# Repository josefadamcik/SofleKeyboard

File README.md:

# Sofle Keyboard

Sofle is 6×4+5 keys column-staggered split keyboard with encoder support. Based on [Lily58](https://github.com/kata0510/Lily58), [Corne](https://github.com/foostan/crkbd) and [Helix](https://github.com/MakotoKurauchi/helix) keyboards.

**[For more information and documentation visit https://josefadamcik.github.io/SofleKeyboard/](https://josefadamcik.github.io/SofleKeyboard/)**

SofleKeyboard was created by [Josef Adamcik](https://josef-adamcik.cz/). The motivation and process is covered in following blog-post: [Let me introduce you SofleKeyboard - a split keyboard based on Lily58 and Crkbd](https://josef-adamcik.cz/electronics/let-me-introduce-you-sofle-keyboard-split-keyboard-based-on-lily58.html)

Sofle RGB was contributed by [Dane Evans](https://github.com/DaneEvans).

Sofle soldered was contributed by [kb-elmo](https://github.com/kb-elmo)

Sofle Pico was contributed by [Ryan Neff](https://github.com/JellyTitan)

BFS9000 was contributed by [Jesús Guillén](https://github.com/jguillen-lab)

## Firmware 

Sofle uses [QMK firmware](https://qmk.fm/)

## Default layout 

## Images of keyboard

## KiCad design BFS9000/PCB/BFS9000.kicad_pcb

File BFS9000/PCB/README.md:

# BFS9000 — Hardware

> 🇪🇸 **¿Prefieres leer esto en español?** ? [README.es.md](README.es.md)

Hardware directory for the **BFS9000** keyboard.

> **Work in progress**
>
> This hardware is currently under active development and is **not functional yet**.
> Version `0.4` should be considered an early prototype intended only for validation and iteration.
>
> Do **not** treat the current design, PCB, schematics, footprints, BOM, or documentation as final or production-ready.
> Expect breaking changes, missing features, design errors, and incomplete documentation.

## Status

- Current version: `0.4`
- Development stage: prototype / WIP
- Functional status: **not working yet**

## Notes

This directory is intended to track the ongoing hardware development of the BFS9000.
At this stage, the project is still evolving and substantial changes are expected before it becomes usable.

## License and attribution

This hardware directory is licensed under the MIT License unless otherwise stated.

BFS9000 contains original work as well as files, ideas, references, or derived work from other open-source keyboard projects and component libraries.

See:

- [LICENSE](LICENSE)
- [NOTICE.md](NOTICE.md)

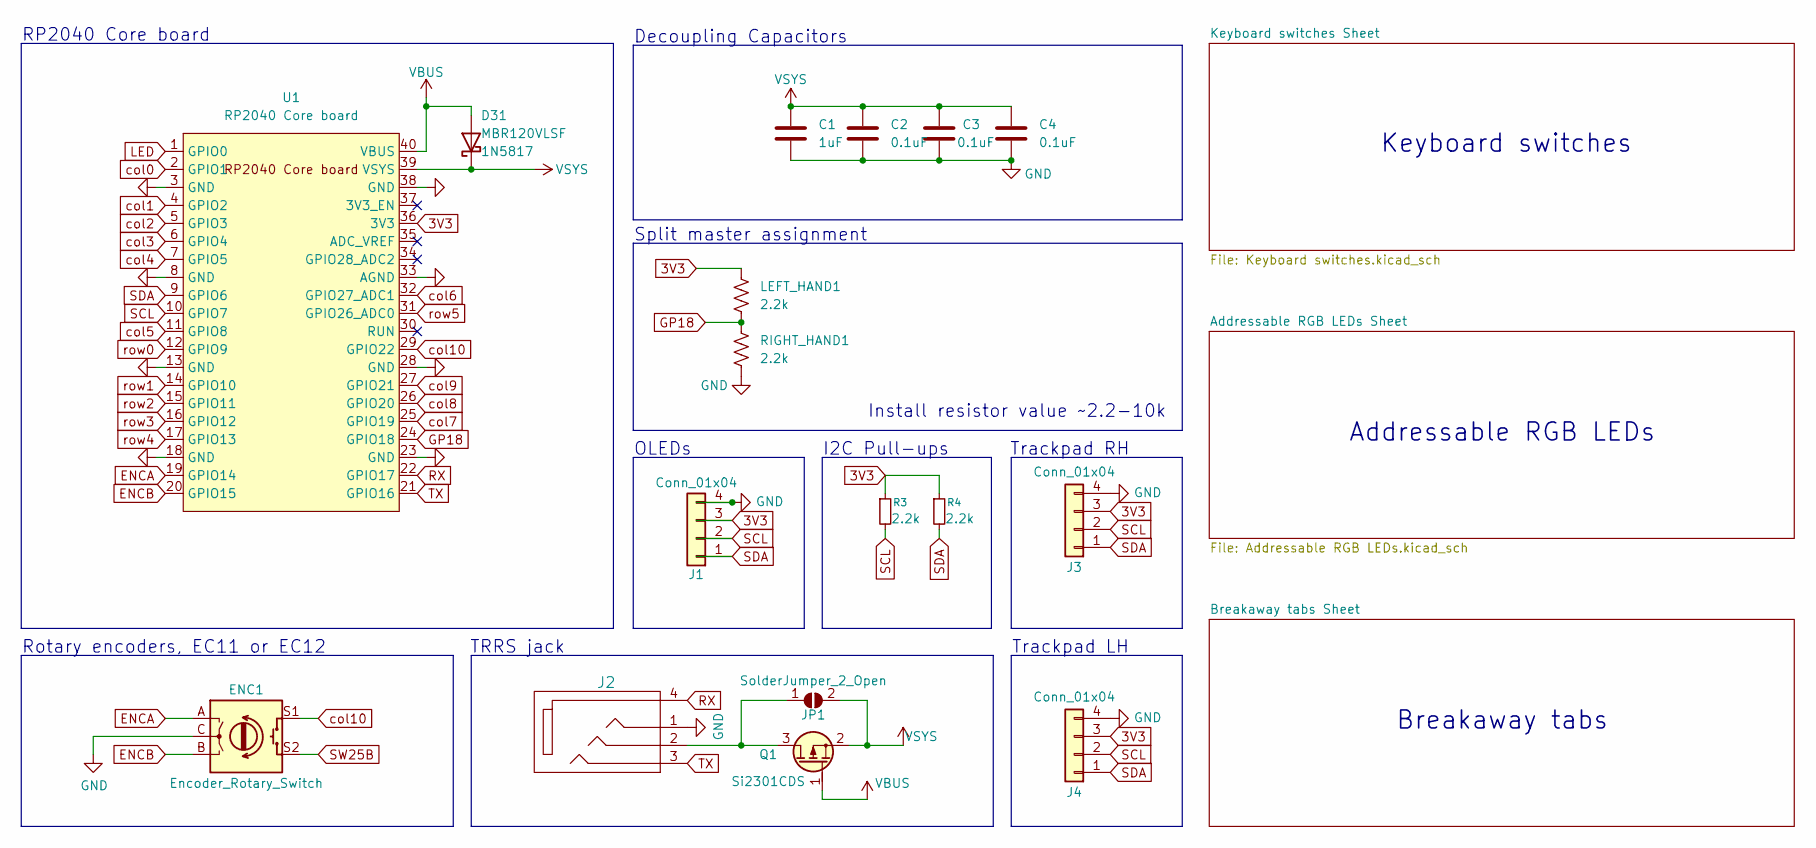
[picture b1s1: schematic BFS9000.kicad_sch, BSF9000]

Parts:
C1: 1uF; C_0805_HandSolder; Tolerance (%) 10; Voltage Rating 50V; MFG PN CL21B105KBFNNNE; JLCPCB_PN C28323
C2, C3, C4: 0.1uF; C_0805_HandSolder; Tolerance (%) 10; Voltage Rating 50V; MFG PN CC0805KRX7R9BB104; JLCPCB_PN C49678
D31: MBR120VLSF; D_Hybrid_SOD-123_DO-41_P7.62mm_DS
ENC1: Encoder_Rotary_Switch; Encoder_EC11E_Switch_Vertical_H20mm; MFG PN EC11E18244AU; JLCPCB_PN C202365
J1: Conn_01x04; Display_OLED_SSD1306_128x64; MFG PN DNP; JLCPCB_PN DNP
J2: MJ-4PP-9; MFG PN PJ-320AS; JLCPCB_PN C2939182
J3, J4: Conn_01x04; Conn_Touchpad; MFG PN DNP; JLCPCB_PN DNP
JP1: SolderJumper_2_Open; SolderJumper_Level_Shifter_Bypass; MFG PN DNP; JLCPCB_PN DNP
LEFT_HAND1: 2.2k; R_Hybrid_1206_P6.3mm; MFG PN CFR-25JB-52-2K2; JLCPCB_PN C1364486
Q1: Si2301CDS; SOT-23_DS; MFG PN SI2301CDS-T1-GE3; JLCPCB_PN C10487
R3, R4: 2.2k; R_Hybrid_1206_P6.3mm; MFG PN CFR-25JB-52-2K2; JLCPCB_PN C1364486
RIGHT_HAND1: 2.2k; R_Hybrid_1206_P6.3mm; MFG PN CFR-25JB-52-2K2; JLCPCB_PN C1364486
U1: RP2040 Core board; RPi_Pico_SMD_TH_DS; MFG PN DNP; JLCPCB_PN DNP

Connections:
3V3: J1.3, J3.3, J4.3, LEFT_HAND1.2, R3.1, R4.1, U1.36 (3V3)
ENCA: ENC1.A, U1.19 (GPIO14)
ENCB: ENC1.B, U1.20 (GPIO15)
GND: C1.2, C2.2, C3.2, C4.2, ENC1.C, J1.4, J2.1, J3.4, J4.4, RIGHT_HAND1.2, U1.3 (GND), U1.8 (GND), U1.13 (GND), U1.18 (GND), U1.23 (GND), U1.28 (GND), U1.33 (AGND), U1.38 (GND); also elsewhere on the board
GP18: LEFT_HAND1.1, RIGHT_HAND1.1, U1.24 (GPIO18)
LED: U1.1 (GPIO0); also elsewhere on the board
unnamed: J2.2, JP1.1 (A), Q1.3 (D)
RX: J2.4, U1.22 (GPIO17)
SCL: J1.2, J3.2, J4.2, R3.2, U1.10 (GPIO7)
SDA: J1.1, J3.1, J4.1, R4.2, U1.9 (GPIO6)
SW25B: ENC1.S2; also elsewhere on the board
TX: J2.3, U1.21 (GPIO16)
VBUS: D31.2 (A), Q1.1 (G), U1.40 (VBUS)
VSYS: C1.1, C2.1, C3.1, C4.1, D31.1 (K), JP1.2 (B), Q1.2 (S), U1.39 (VSYS); also elsewhere on the board
col0: U1.2 (GPIO1); also elsewhere on the board
col1: U1.4 (GPIO2); also elsewhere on the board
col2: U1.5 (GPIO3); also elsewhere on the board
col3: U1.6 (GPIO4); also elsewhere on the board
col4: U1.7 (GPIO5); also elsewhere on the board
col5: U1.11 (GPIO8); also elsewhere on the board
col6: U1.32 (GPIO27_ADC1); also elsewhere on the board
col7: U1.25 (GPIO19); also elsewhere on the board
col8: U1.26 (GPIO20); also elsewhere on the board
col9: U1.27 (GPIO21); also elsewhere on the board
col10: ENC1.S1, U1.29 (GPIO22); also elsewhere on the board
row0: U1.12 (GPIO9); also elsewhere on the board
row1: U1.14 (GPIO10); also elsewhere on the board
row2: U1.15 (GPIO11); also elsewhere on the board
row3: U1.16 (GPIO12); also elsewhere on the board
row4: U1.17 (GPIO13); also elsewhere on the board
row5: U1.31 (GPIO26_ADC0); also elsewhere on the board

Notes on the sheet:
Rotary encoders, EC11 or EC12
OLEDs
Install resistor value ~2.2-10k
Split master assignment
I2C Pull-ups
Breakaway tabs
TRRS jack
Keyboard switches
RP2040 Core board
Trackpad LH
Trackpad RH
Addressable RGB LEDs
Decoupling Capacitors

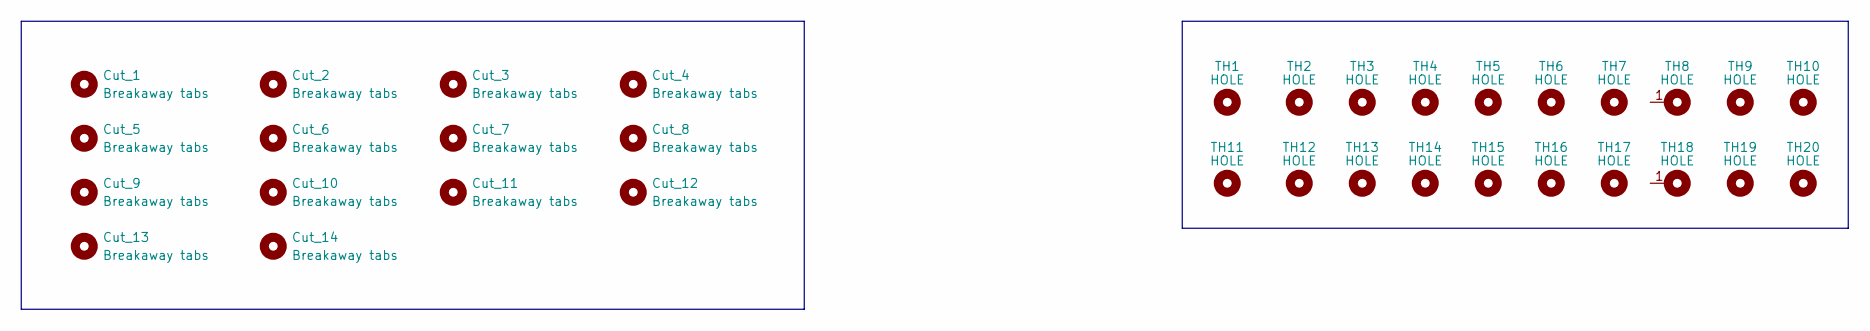
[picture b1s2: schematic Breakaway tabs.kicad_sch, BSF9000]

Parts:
Cut_1, Cut_2, Cut_3, Cut_4, Cut_5, Cut_6, Cut_7, Cut_8, Cut_9, Cut_10, Cut_11, Cut_12, Cut_13, Cut_14: Breakaway tabs; Cutout_Long_Oval; MFR.Part # DNP; JLCPCB Part # DNP
TH1, TH2, TH4, TH5: HOLE; Mount_M2_Post_Hole_Keyplate_Narrow; MFG PN DNP; JLCPCB_PN DNP
TH3, TH6, TH7, TH9, TH10, TH11, TH12, TH13, TH14, TH15, TH16, TH17, TH19, TH20: HOLE; Mount_M2_Post_Hole_Keyplate_Wide; MFG PN DNP; JLCPCB_PN DNP
TH8, TH18: HOLE; Mount_Tenting_Puck; MFG PN DNP; JLCPCB_PN DNP

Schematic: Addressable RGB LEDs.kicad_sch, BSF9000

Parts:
J5, J6: Conn_01x01; PinHeader_1x01_P2.54mm; MFG PN DNP; JLCPCB_PN DNP
MLED1, MLED2, MLED3, MLED4, MLED5, MLED6, MLED7, MLED8, MLED9, MLED10, MLED11, MLED12, MLED13, MLED14, MLED15, MLED16, MLED17, MLED18, MLED19, MLED20, MLED21, MLED22, MLED23, MLED24, MLED25, MLED26, MLED27, MLED28, MLED29: SK6803 MINI-E; Cust_SK6803_MINI-E_BFS9000; MFG PN SK6803MINI-E-001; JLCPCB_PN C5242955
MULED1, MULED2, MULED3: SK6803 MINI-E; Cust_SK6803_MINI-E_BFS9000_Underglow; MFG PN SK6803MINI-E-001; JLCPCB_PN C5242955
SLED1, SLED2, SLED3, SLED4, SLED5, SLED6, SLED7, SLED8, SLED9, SLED10, SLED11, SLED12, SLED13, SLED14, SLED15, SLED16, SLED17, SLED18, SLED19, SLED20, SLED21, SLED22: SK6803 MINI-E; Cust_SK6803_MINI-E_BFS9000; MFG PN SK6803MINI-E-001; JLCPCB_PN C5242955
SULED1, SULED2: SK6803 MINI-E; Cust_SK6803_MINI-E_BFS9000_Underglow; MFG PN SK6803MINI-E-001; JLCPCB_PN C5242955
TLED1, TLED2, TLED3, TLED4, TLED5, TLED6: SK6803 MINI-E; Cust_SK6803_MINI-E_BFS9000; MFG PN SK6803MINI-E-001; JLCPCB_PN C5242955

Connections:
GND: MLED1.1 (GND), MLED2.1 (GND), MLED3.1 (GND), MLED4.1 (GND), MLED5.1 (GND), MLED6.1 (GND), MLED7.1 (GND), MLED8.1 (GND), MLED9.1 (GND), MLED10.1 (GND), MLED11.1 (GND), MLED12.1 (GND), MLED13.1 (GND), MLED14.1 (GND), MLED15.1 (GND), MLED16.1 (GND), MLED17.1 (GND), MLED18.1 (GND), MLED19.1 (GND), MLED20.1 (GND), MLED21.1 (GND), MLED22.1 (GND), MLED23.1 (GND), MLED24.1 (GND), MLED25.1 (GND), MLED26.1 (GND), MLED27.1 (GND), MLED28.1 (GND), MLED29.1 (GND), MULED1.1 (GND), MULED2.1 (GND), MULED3.1 (GND), SLED1.1 (GND), SLED2.1 (GND), SLED3.1 (GND), SLED4.1 (GND), SLED5.1 (GND), SLED6.1 (GND), SLED7.1 (GND), SLED8.1 (GND), SLED9.1 (GND), SLED10.1 (GND), SLED11.1 (GND), SLED12.1 (GND), SLED13.1 (GND), SLED14.1 (GND), SLED15.1 (GND), SLED16.1 (GND), SLED17.1 (GND), SLED18.1 (GND), SLED19.1 (GND), SLED20.1 (GND), SLED21.1 (GND), SLED22.1 (GND), SULED1.1 (GND), SULED2.1 (GND), TLED1.1 (GND), TLED2.1 (GND), TLED3.1 (GND), TLED4.1 (GND), TLED5.1 (GND), TLED6.1 (GND); also elsewhere on the board
LED: MLED1.2 (DIN); also elsewhere on the board
LED_N: J6.1 (Pin_1_1), SLED1.2 (DIN), TLED6.4 (DOUT)
LED_T: J5.1 (Pin_1_1), MULED3.4 (DOUT), TLED1.2 (DIN)
LED_U: MLED29.4 (DOUT), MULED1.2 (DIN)
unnamed: MLED1.4 (DOUT), MLED2.2 (DIN)
unnamed: MLED2.4 (DOUT), MLED3.2 (DIN)
unnamed: MLED3.4 (DOUT), MLED4.2 (DIN)
unnamed: MLED4.4 (DOUT), MLED5.2 (DIN)
unnamed: MLED5.4 (DOUT), MLED6.2 (DIN)
unnamed: MLED6.4 (DOUT), MLED7.2 (DIN)
unnamed: MLED7.4 (DOUT), MLED8.2 (DIN)
unnamed: MLED8.4 (DOUT), MLED9.2 (DIN)
unnamed: MLED9.4 (DOUT), MLED10.2 (DIN)
unnamed: MLED10.4 (DOUT), MLED11.2 (DIN)
unnamed: MLED11.4 (DOUT), MLED12.2 (DIN)
unnamed: MLED12.4 (DOUT), MLED13.2 (DIN)
unnamed: MLED13.4 (DOUT), MLED14.2 (DIN)
unnamed: MLED14.4 (DOUT), MLED15.2 (DIN)
unnamed: MLED15.4 (DOUT), MLED16.2 (DIN)
unnamed: MLED16.4 (DOUT), MLED17.2 (DIN)
unnamed: MLED17.4 (DOUT), MLED18.2 (DIN)
unnamed: MLED18.4 (DOUT), MLED19.2 (DIN)
unnamed: MLED19.4 (DOUT), MLED20.2 (DIN)
unnamed: MLED20.4 (DOUT), MLED21.2 (DIN)
unnamed: MLED21.4 (DOUT), MLED22.2 (DIN)
unnamed: MLED22.4 (DOUT), MLED23.2 (DIN)
unnamed: MLED23.4 (DOUT), MLED24.2 (DIN)
unnamed: MLED24.4 (DOUT), MLED25.2 (DIN)
unnamed: MLED25.4 (DOUT), MLED26.2 (DIN)
unnamed: MLED26.4 (DOUT), MLED27.2 (DIN)
unnamed: MLED27.4 (DOUT), MLED28.2 (DIN)
unnamed: MLED28.4 (DOUT), MLED29.2 (DIN)
unnamed: MULED1.4 (DOUT), MULED2.2 (DIN)
unnamed: MULED2.4 (DOUT), MULED3.2 (DIN)
unnamed: SLED1.4 (DOUT), SLED2.2 (DIN)
unnamed: SLED2.4 (DOUT), SLED3.2 (DIN)
unnamed: SLED3.4 (DOUT), SLED4.2 (DIN)
unnamed: SLED4.4 (DOUT), SLED5.2 (DIN)
unnamed: SLED5.4 (DOUT), SLED6.2 (DIN)
unnamed: SLED6.4 (DOUT), SLED7.2 (DIN)
unnamed: SLED7.4 (DOUT), SLED8.2 (DIN)
unnamed: SLED8.4 (DOUT), SLED9.2 (DIN)
unnamed: SLED9.4 (DOUT), SLED10.2 (DIN)
unnamed: SLED10.4 (DOUT), SLED11.2 (DIN)
unnamed: SLED11.4 (DOUT), SLED12.2 (DIN)
unnamed: SLED12.4 (DOUT), SLED13.2 (DIN)
unnamed: SLED13.4 (DOUT), SLED14.2 (DIN)
unnamed: SLED14.4 (DOUT), SLED15.2 (DIN)
unnamed: SLED15.4 (DOUT), SLED16.2 (DIN)
unnamed: SLED16.4 (DOUT), SLED17.2 (DIN)
unnamed: SLED17.4 (DOUT), SLED18.2 (DIN)
unnamed: SLED18.4 (DOUT), SLED19.2 (DIN)
unnamed: SLED19.4 (DOUT), SLED20.2 (DIN)
unnamed: SLED20.4 (DOUT), SLED21.2 (DIN)
unnamed: SLED21.4 (DOUT), SLED22.2 (DIN)
unnamed: SULED1.4 (DOUT), SULED2.2 (DIN)
unnamed: TLED1.4 (DOUT), TLED2.2 (DIN)
unnamed: TLED2.4 (DOUT), TLED3.2 (DIN)
unnamed: TLED3.4 (DOUT), TLED4.2 (DIN)
unnamed: TLED4.4 (DOUT), TLED5.2 (DIN)
unnamed: TLED5.4 (DOUT), TLED6.2 (DIN)
VSYS: MLED1.3 (VDD), MLED2.3 (VDD), MLED3.3 (VDD), MLED4.3 (VDD), MLED5.3 (VDD), MLED6.3 (VDD), MLED7.3 (VDD), MLED8.3 (VDD), MLED9.3 (VDD), MLED10.3 (VDD), MLED11.3 (VDD), MLED12.3 (VDD), MLED13.3 (VDD), MLED14.3 (VDD), MLED15.3 (VDD), MLED16.3 (VDD), MLED17.3 (VDD), MLED18.3 (VDD), MLED19.3 (VDD), MLED20.3 (VDD), MLED21.3 (VDD), MLED22.3 (VDD), MLED23.3 (VDD), MLED24.3 (VDD), MLED25.3 (VDD), MLED26.3 (VDD), MLED27.3 (VDD), MLED28.3 (VDD), MLED29.3 (VDD), MULED1.3 (VDD), MULED2.3 (VDD), MULED3.3 (VDD), SLED1.3 (VDD), SLED2.3 (VDD), SLED3.3 (VDD), SLED4.3 (VDD), SLED5.3 (VDD), SLED6.3 (VDD), SLED7.3 (VDD), SLED8.3 (VDD), SLED9.3 (VDD), SLED10.3 (VDD), SLED11.3 (VDD), SLED12.3 (VDD), SLED13.3 (VDD), SLED14.3 (VDD), SLED15.3 (VDD), SLED16.3 (VDD), SLED17.3 (VDD), SLED18.3 (VDD), SLED19.3 (VDD), SLED20.3 (VDD), SLED21.3 (VDD), SLED22.3 (VDD), SULED1.3 (VDD), SULED2.3 (VDD), TLED1.3 (VDD), TLED2.3 (VDD), TLED3.3 (VDD), TLED4.3 (VDD), TLED5.3 (VDD), TLED6.3 (VDD); also elsewhere on the board
nLED_U: SLED22.4 (DOUT), SULED1.2 (DIN)

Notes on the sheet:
All LEDs

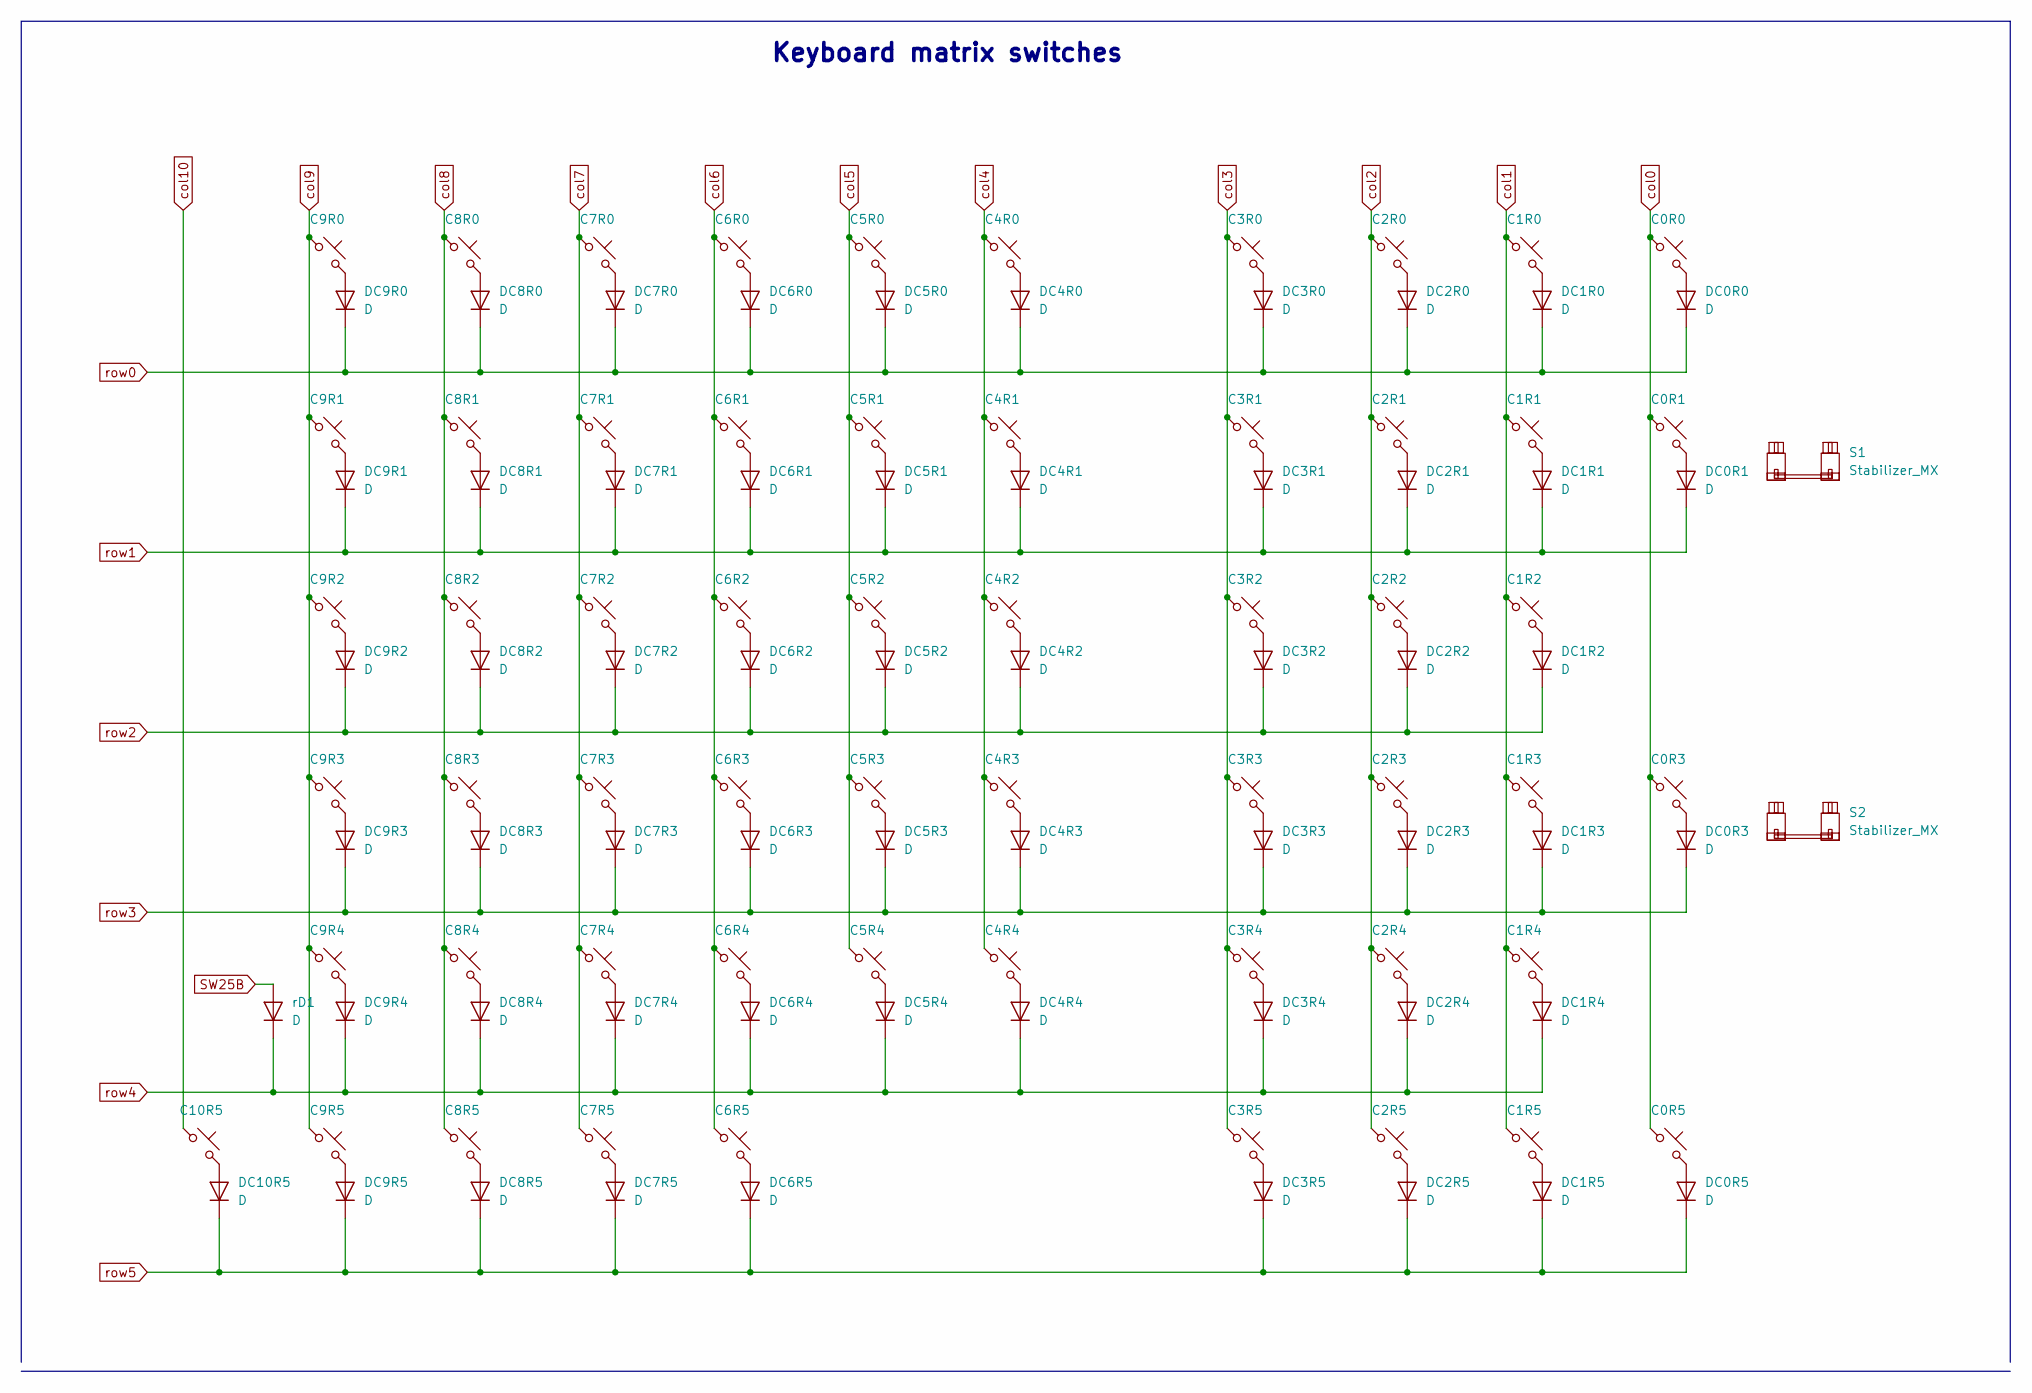
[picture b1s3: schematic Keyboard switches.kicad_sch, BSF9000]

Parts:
C0R0, C0R1, C0R3, C0R5, C1R0, C1R1, C1R2, C1R3, C1R4, C1R5, C2R0, C2R1, C2R2, C2R3, C2R4, C2R5, C3R0, C3R1, C3R2, C3R3, C3R4, C3R5, C4R0, C4R1, C4R2, C4R3, C4R4, C5R0, C5R1, C5R2, C5R3, C5R4, C6R0, C6R1, C6R2, C6R3, C6R4, C6R5, C7R0, C7R1, C7R2, C7R3, C7R4, C7R5, C8R0, C8R1, C8R2, C8R3, C8R4, C8R5, C9R0, C9R1, C9R2, C9R3, C9R4, C9R5, C10R5: MX_SW_HS; SW_Cherry_MX_Hotswap_DS; MFG PN CPG151101S11-16; JLCPCB_PN C41430893
DC0R0, DC0R1, DC0R3, DC0R5, DC1R0, DC1R1, DC1R2, DC1R3, DC1R4, DC1R5, DC2R0, DC2R1, DC2R2, DC2R3, DC2R4, DC2R5, DC3R0, DC3R1, DC3R2, DC3R3, DC3R4, DC3R5, DC4R0, DC4R1, DC4R2, DC4R3, DC4R4, DC5R0, DC5R1, DC5R2, DC5R3, DC5R4, DC6R0, DC6R1, DC6R2, DC6R3, DC6R4, DC6R5, DC7R0, DC7R1, DC7R2, DC7R3, DC7R4, DC7R5, DC8R0, DC8R1, DC8R2, DC8R3, DC8R4, DC8R5, DC9R0, DC9R1, DC9R2, DC9R3, DC9R4, DC9R5, DC10R5: D; D_Hybrid_SOD-123_DO-35_DS; Voltage Rating 75v; MFG PN 1N4148W; JLCPCB_PN C81598
S1, S2: Stabilizer_MX; Stabilizer_MX_2u; MFG PN DNP; JLCPCB_PN DNP
rD1: D; D_Hybrid_SOD-123_DO-35_DS; Voltage Rating 75v; MFG PN 1N4148W; JLCPCB_PN C81598

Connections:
unnamed: C0R0.2, DC0R0.2 (A)
unnamed: C0R1.2, DC0R1.2 (A)
unnamed: C0R3.2, DC0R3.2 (A)
unnamed: C0R5.2, DC0R5.2 (A)
unnamed: C1R0.2, DC1R0.2 (A)
unnamed: C1R1.2, DC1R1.2 (A)
unnamed: C1R2.2, DC1R2.2 (A)
unnamed: C1R3.2, DC1R3.2 (A)
unnamed: C1R4.2, DC1R4.2 (A)
unnamed: C1R5.2, DC1R5.2 (A)
unnamed: C2R0.2, DC2R0.2 (A)
unnamed: C2R1.2, DC2R1.2 (A)
unnamed: C2R2.2, DC2R2.2 (A)
unnamed: C2R3.2, DC2R3.2 (A)
unnamed: C2R4.2, DC2R4.2 (A)
unnamed: C2R5.2, DC2R5.2 (A)
unnamed: C3R0.2, DC3R0.2 (A)
unnamed: C3R1.2, DC3R1.2 (A)
unnamed: C3R2.2, DC3R2.2 (A)
unnamed: C3R3.2, DC3R3.2 (A)
unnamed: C3R4.2, DC3R4.2 (A)
unnamed: C3R5.2, DC3R5.2 (A)
unnamed: C4R0.2, DC4R0.2 (A)
unnamed: C4R1.2, DC4R1.2 (A)
unnamed: C4R2.2, DC4R2.2 (A)
unnamed: C4R3.2, DC4R3.2 (A)
unnamed: C4R4.2, DC4R4.2 (A)
unnamed: C5R0.2, DC5R0.2 (A)
unnamed: C5R1.2, DC5R1.2 (A)
unnamed: C5R2.2, DC5R2.2 (A)
unnamed: C5R3.2, DC5R3.2 (A)
unnamed: C5R4.2, DC5R4.2 (A)
unnamed: C6R0.2, DC6R0.2 (A)
unnamed: C6R1.2, DC6R1.2 (A)
unnamed: C6R2.2, DC6R2.2 (A)
unnamed: C6R3.2, DC6R3.2 (A)
unnamed: C6R4.2, DC6R4.2 (A)
unnamed: C6R5.2, DC6R5.2 (A)
unnamed: C7R0.2, DC7R0.2 (A)
unnamed: C7R1.2, DC7R1.2 (A)
unnamed: C7R2.2, DC7R2.2 (A)
unnamed: C7R3.2, DC7R3.2 (A)
unnamed: C7R4.2, DC7R4.2 (A)
unnamed: C7R5.2, DC7R5.2 (A)
unnamed: C8R0.2, DC8R0.2 (A)
unnamed: C8R1.2, DC8R1.2 (A)
unnamed: C8R2.2, DC8R2.2 (A)
unnamed: C8R3.2, DC8R3.2 (A)
unnamed: C8R4.2, DC8R4.2 (A)
unnamed: C8R5.2, DC8R5.2 (A)
unnamed: C9R0.2, DC9R0.2 (A)
unnamed: C9R1.2, DC9R1.2 (A)
unnamed: C9R2.2, DC9R2.2 (A)
unnamed: C9R3.2, DC9R3.2 (A)
unnamed: C9R4.2, DC9R4.2 (A)
unnamed: C9R5.2, DC9R5.2 (A)
unnamed: C10R5.2, DC10R5.2 (A)
SW25B: rD1.2 (A); also elsewhere on the board
col0: C0R0.1, C0R1.1, C0R3.1, C0R5.1; also elsewhere on the board
col1: C1R0.1, C1R1.1, C1R2.1, C1R3.1, C1R4.1, C1R5.1; also elsewhere on the board
col2: C2R0.1, C2R1.1, C2R2.1, C2R3.1, C2R4.1, C2R5.1; also elsewhere on the board
col3: C3R0.1, C3R1.1, C3R2.1, C3R3.1, C3R4.1, C3R5.1; also elsewhere on the board
col4: C4R0.1, C4R1.1, C4R2.1, C4R3.1, C4R4.1; also elsewhere on the board
col5: C5R0.1, C5R1.1, C5R2.1, C5R3.1, C5R4.1; also elsewhere on the board
col6: C6R0.1, C6R1.1, C6R2.1, C6R3.1, C6R4.1, C6R5.1; also elsewhere on the board
col7: C7R0.1, C7R1.1, C7R2.1, C7R3.1, C7R4.1, C7R5.1; also elsewhere on the board
col8: C8R0.1, C8R1.1, C8R2.1, C8R3.1, C8R4.1, C8R5.1; also elsewhere on the board
col9: C9R0.1, C9R1.1, C9R2.1, C9R3.1, C9R4.1, C9R5.1; also elsewhere on the board
col10: C10R5.1; also elsewhere on the board
row0: DC0R0.1 (K), DC1R0.1 (K), DC2R0.1 (K), DC3R0.1 (K), DC4R0.1 (K), DC5R0.1 (K), DC6R0.1 (K), DC7R0.1 (K), DC8R0.1 (K), DC9R0.1 (K); also elsewhere on the board
row1: DC0R1.1 (K), DC1R1.1 (K), DC2R1.1 (K), DC3R1.1 (K), DC4R1.1 (K), DC5R1.1 (K), DC6R1.1 (K), DC7R1.1 (K), DC8R1.1 (K), DC9R1.1 (K); also elsewhere on the board
row2: DC1R2.1 (K), DC2R2.1 (K), DC3R2.1 (K), DC4R2.1 (K), DC5R2.1 (K), DC6R2.1 (K), DC7R2.1 (K), DC8R2.1 (K), DC9R2.1 (K); also elsewhere on the board
row3: DC0R3.1 (K), DC1R3.1 (K), DC2R3.1 (K), DC3R3.1 (K), DC4R3.1 (K), DC5R3.1 (K), DC6R3.1 (K), DC7R3.1 (K), DC8R3.1 (K), DC9R3.1 (K); also elsewhere on the board
row4: DC1R4.1 (K), DC2R4.1 (K), DC3R4.1 (K), DC4R4.1 (K), DC5R4.1 (K), DC6R4.1 (K), DC7R4.1 (K), DC8R4.1 (K), DC9R4.1 (K), rD1.1 (K); also elsewhere on the board
row5: DC0R5.1 (K), DC1R5.1 (K), DC2R5.1 (K), DC3R5.1 (K), DC6R5.1 (K), DC7R5.1 (K), DC8R5.1 (K), DC9R5.1 (K), DC10R5.1 (K); also elsewhere on the board

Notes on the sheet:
Keyboard matrix switches

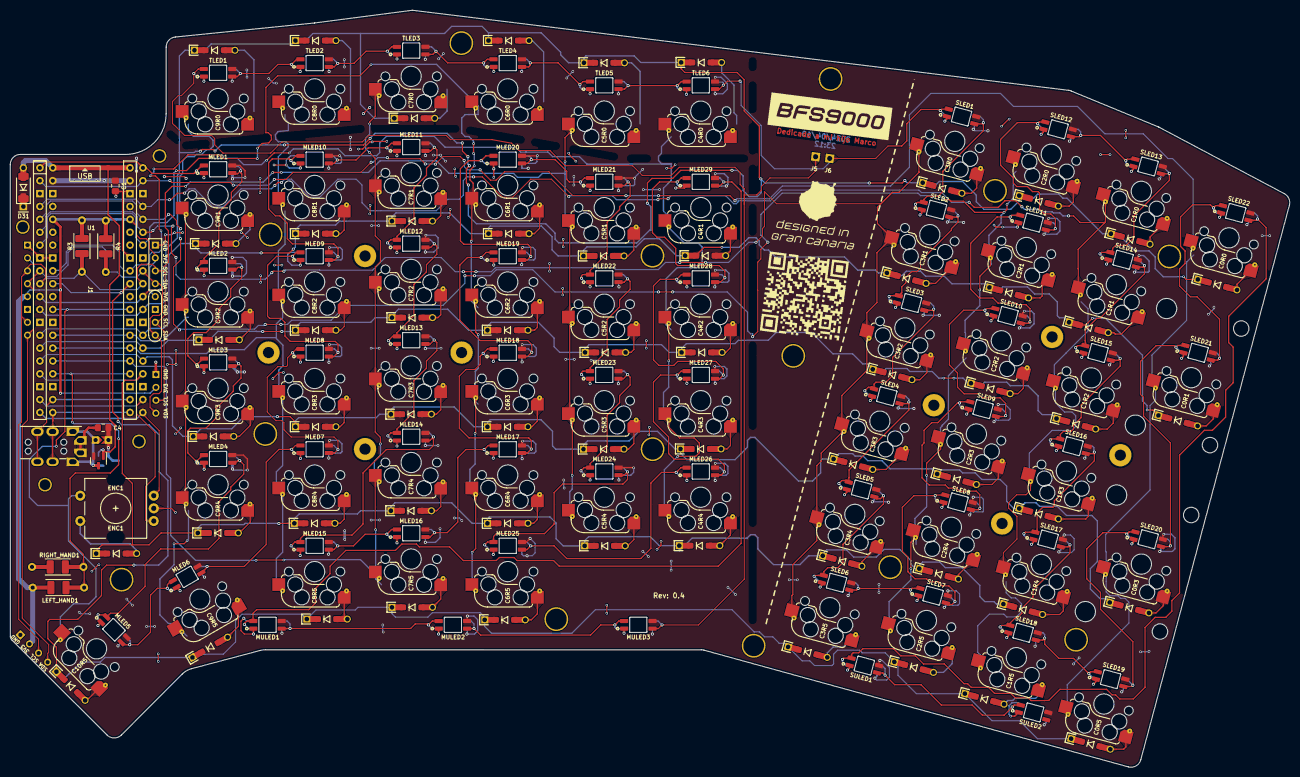
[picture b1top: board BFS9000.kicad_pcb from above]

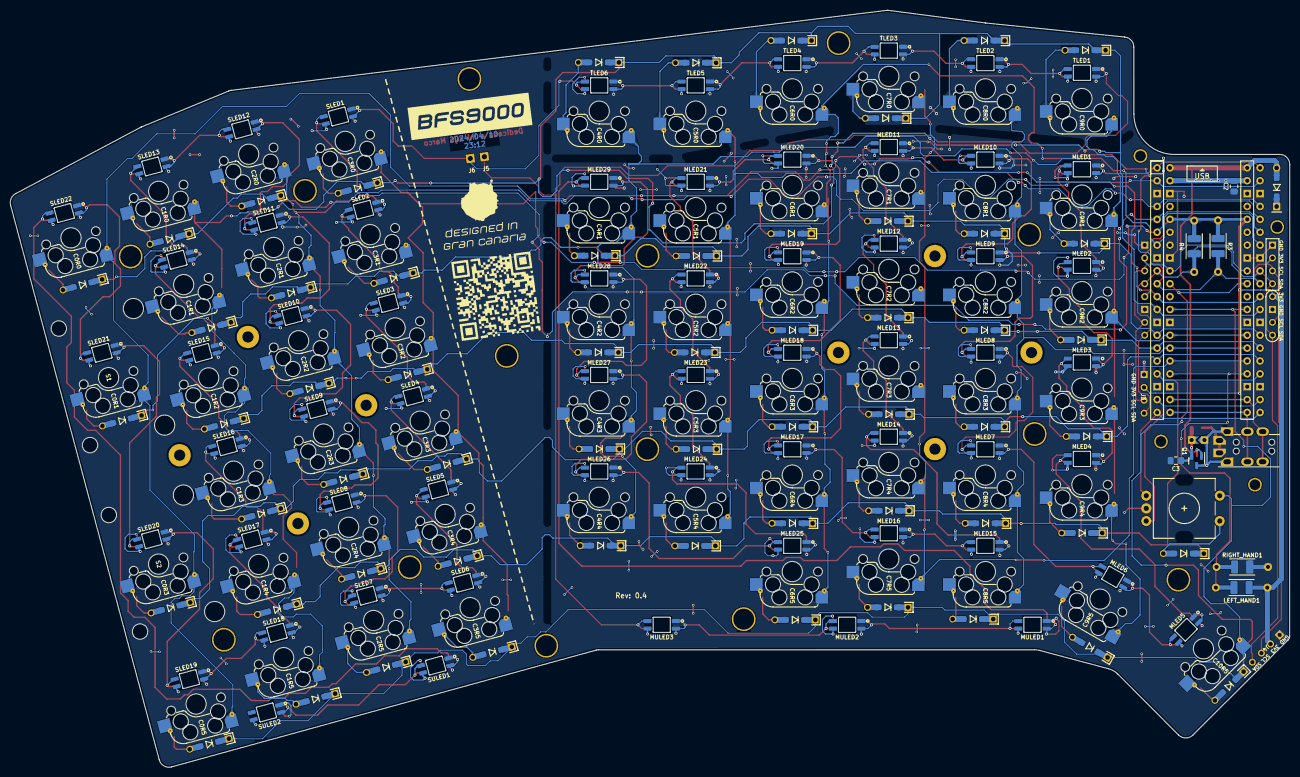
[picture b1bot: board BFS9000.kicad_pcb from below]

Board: 2 copper layers, 252.5 x 149.4 mm, 237 parts (188 on the bottom side), 149 nets.

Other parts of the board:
BFS9000_Back, BFS9000_Front: LOGO; Logo_BFS9000_Gran_Canaria
D31_B: D_SOD-128
Wiki_Back: QR; QR_Wiki
Wiki_Front: QR; QR_Wiki

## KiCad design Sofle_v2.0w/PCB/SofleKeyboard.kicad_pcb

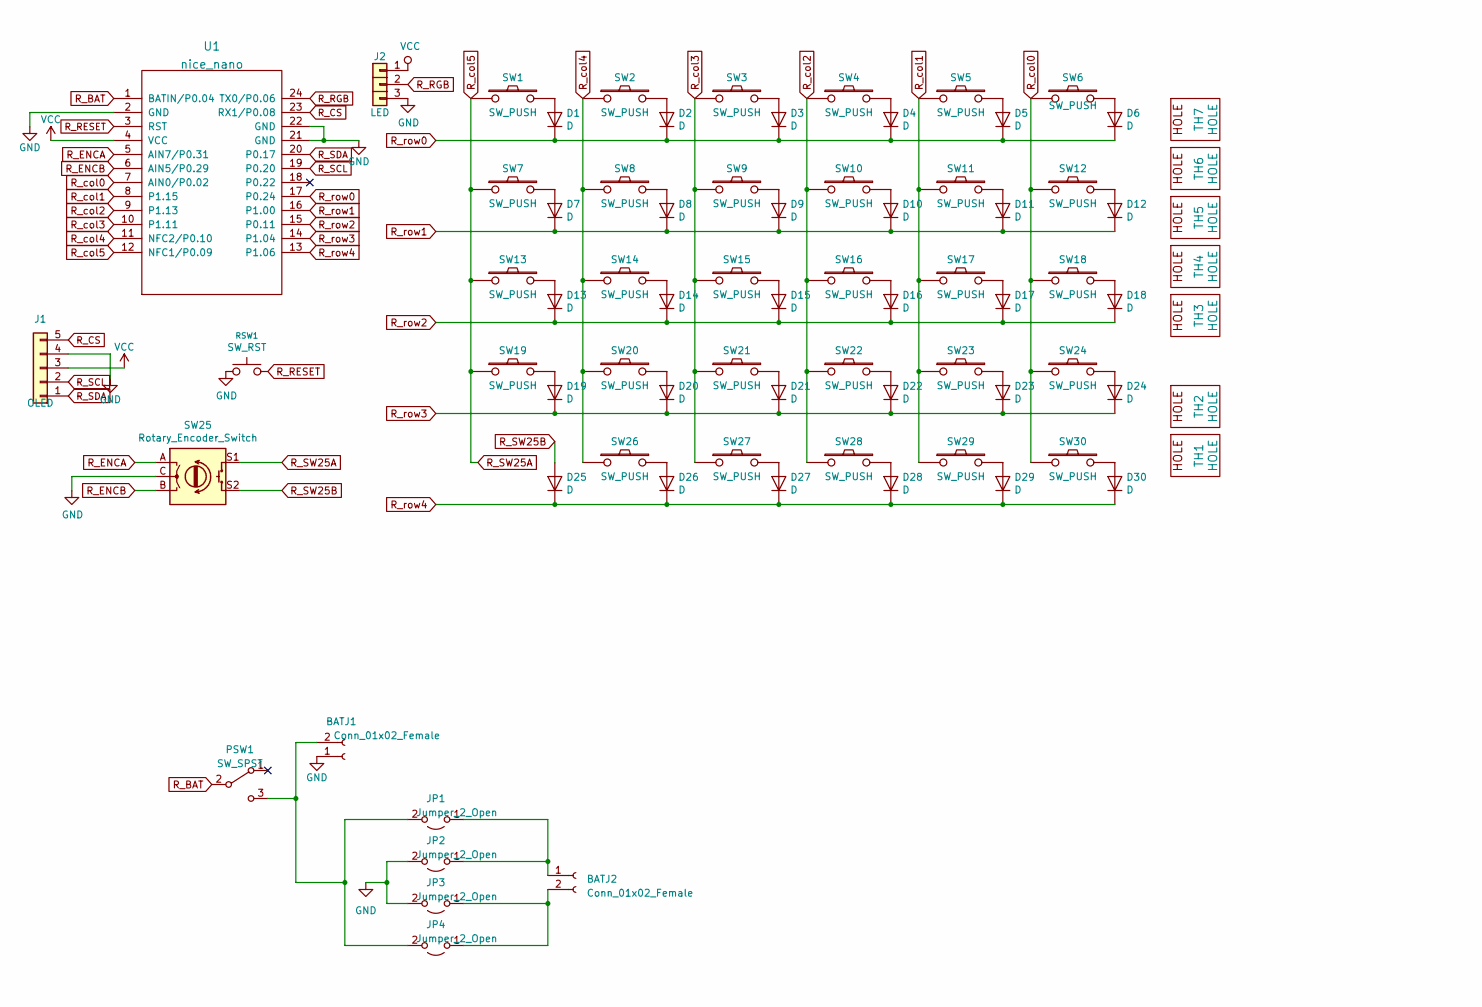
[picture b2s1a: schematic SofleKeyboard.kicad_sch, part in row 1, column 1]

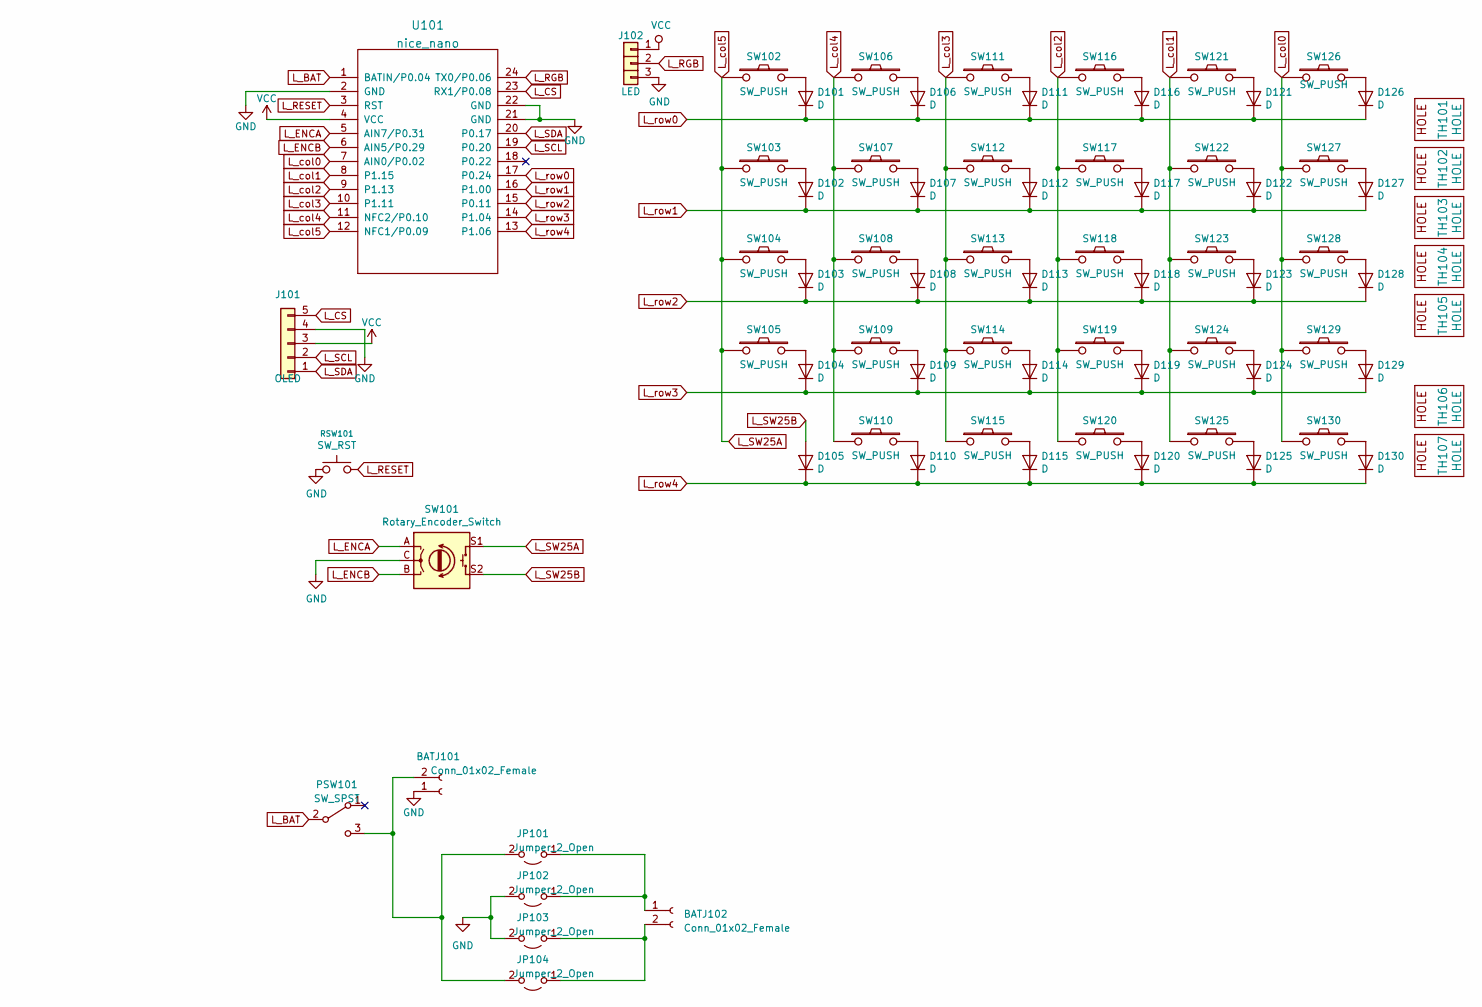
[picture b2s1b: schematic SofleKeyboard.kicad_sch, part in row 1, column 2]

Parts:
BATJ1, BATJ101: Conn_01x02_Female; PinHeader_1x02_P2.54mm_Vertical
BATJ2, BATJ102: Conn_01x02_Female; JST_PH_S2B-PH-K_1x02_P2.00mm_Horizontal
D1, D2, D3, D4, D5, D6, D7, D8, D9, D10, D11, D12, D13, D14, D15, D16, D17, D18, D19, D20, D21, D22, D23, D24, D25, D26, D27, D28, D29, D30, D101, D102, D103, D104, D105, D106, D107, D108, D109, D110, D111, D112, D113, D114, D115, D116, D117, D118, D119, D120, D121, D122, D123, D124, D125, D126, D127, D128, D129, D130: D; Diode_SOD123
J1, J101: OLED; nice_view
J2, J102: LED
JP1, JP2, JP3, JP4, JP101, JP102, JP103, JP104: Jumper_2_Open; SolderJumper-2_P1.3mm_Open_Pad1.0x1.5mm
PSW1, PSW101: SW_SPST; SW_SPDT_PCM12
RSW1, RSW101: SW_RST; TACT_SWITCH_TVBP06
SW1, SW2, SW3, SW4, SW5, SW6, SW7, SW8, SW9, SW10, SW11, SW12, SW13, SW14, SW15, SW16, SW17, SW18, SW19, SW20, SW21, SW22, SW23, SW24, SW27, SW28, SW29, SW30, SW102, SW103, SW104, SW105, SW106, SW107, SW108, SW109, SW111, SW112, SW113, SW114, SW115, SW116, SW117, SW118, SW119, SW120, SW121, SW122, SW123, SW124, SW125, SW126, SW127, SW128, SW129, SW130: SW_PUSH; CherryMX_KailhLowProfile_Hotswap_OneSide
SW25, SW101: Rotary_Encoder_Switch; RotaryEncoder_Alps_EC11E-Switch_Vertical_H20mm-keebio_modif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
SW26, SW110: SW_PUSH; CherryMX_KailhLowProfile_Hotswap_OneSide_1.5
TH1, TH2, TH106, TH107: HOLE; M2_HOLE_PCB
TH3, TH4, TH5, TH6, TH7, TH101, TH102, TH103, TH104, TH105: HOLE; HOLE_M2_TH
U1, U101: nice_nano; nice!nano

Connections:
GND: BATJ1.1, BATJ2.1, BATJ101.1, J1.4, J2.3, J2.4, J101.4, J102.3, JP1.1 (A), JP2.1 (A), JP2.2 (B), JP3.2 (B), JP101.1 (A), JP102.1 (A), JP102.2 (B), JP103.2 (B), RSW1.1, RSW101.1, SW25.C, SW101.C, U1.2 (GND), U1.21 (GND), U1.22 (GND), U101.2 (GND), U101.21 (GND), U101.22 (GND)
L_BAT: PSW101.2 (B), U101.1 (BATIN/P0.04)
L_CS: J101.5, U101.23 (RX1/P0.08)
L_ENCA: SW101.A, U101.5 (AIN7/P0.31)
L_ENCB: SW101.B, U101.6 (AIN5/P0.29)
L_RESET: RSW101.2, U101.3 (RST)
L_RGB: J102.2, U101.24 (TX0/P0.06)
L_SCL: J101.2, U101.19 (P0.20)
L_SDA: J101.1, U101.20 (P0.17)
L_SW25A: SW101.S1, SW102.1, SW103.1, SW104.1, SW105.1, U101.12 (NFC1/P0.09)
L_SW25B: D105.2 (A), SW101.S2
L_col0: SW126.1, SW127.1, SW128.1, SW129.1, SW130.1, U101.7 (AIN0/P0.02)
L_col1: SW121.1, SW122.1, SW123.1, SW124.1, SW125.1, U101.8 (P1.15)
L_col2: SW116.1, SW117.1, SW118.1, SW119.1, SW120.1, U101.9 (P1.13)
L_col3: SW111.1, SW112.1, SW113.1, SW114.1, SW115.1, U101.10 (P1.11)
L_col4: SW106.1, SW107.1, SW108.1, SW109.1, SW110.1, U101.11 (NFC2/P0.10)
L_row0: D101.1 (K), D106.1 (K), D111.1 (K), D116.1 (K), D121.1 (K), D126.1 (K), U101.17 (P0.24)
L_row1: D102.1 (K), D107.1 (K), D112.1 (K), D117.1 (K), D122.1 (K), D127.1 (K), U101.16 (P1.00)
L_row2: D103.1 (K), D108.1 (K), D113.1 (K), D118.1 (K), D123.1 (K), D128.1 (K), U101.15 (P0.11)
L_row3: D104.1 (K), D109.1 (K), D114.1 (K), D119.1 (K), D124.1 (K), D129.1 (K), U101.14 (P1.04)
L_row4: D105.1 (K), D110.1 (K), D115.1 (K), D120.1 (K), D125.1 (K), D130.1 (K), U101.13 (P1.06)
unnamed: BATJ1.2, BATJ2.2, JP1.2 (B), JP3.1 (A), JP4.1 (A), JP4.2 (B), JP103.1 (A), JP104.1 (A), PSW1.3 (C)
unnamed: BATJ101.2, PSW101.3 (C)
unnamed: D1.2 (A), SW1.2
unnamed: D2.2 (A), SW2.2
unnamed: D3.2 (A), SW3.2
unnamed: D4.2 (A), SW4.2
unnamed: D5.2 (A), SW5.2
unnamed: D6.2 (A), SW6.2
unnamed: D7.2 (A), SW7.2
unnamed: D8.2 (A), SW8.2
unnamed: D9.2 (A), SW9.2
unnamed: D10.2 (A), SW10.2
unnamed: D11.2 (A), SW11.2
unnamed: D12.2 (A), SW12.2
unnamed: D13.2 (A), SW13.2
unnamed: D14.2 (A), SW14.2
unnamed: D15.2 (A), SW15.2
unnamed: D16.2 (A), SW16.2
unnamed: D17.2 (A), SW17.2
unnamed: D18.2 (A), SW18.2
unnamed: D19.2 (A), SW19.2
unnamed: D20.2 (A), SW20.2
unnamed: D21.2 (A), SW21.2
unnamed: D22.2 (A), SW22.2
unnamed: D23.2 (A), SW23.2
unnamed: D24.2 (A), SW24.2
unnamed: D26.2 (A), SW26.2
unnamed: D27.2 (A), SW27.2
unnamed: D28.2 (A), SW28.2
unnamed: D29.2 (A), SW29.2
unnamed: D30.2 (A), SW30.2
unnamed: D101.2 (A), SW102.2
unnamed: D102.2 (A), SW103.2
unnamed: D103.2 (A), SW104.2
unnamed: D104.2 (A), SW105.2
unnamed: D106.2 (A), SW106.2
unnamed: D107.2 (A), SW107.2
unnamed: D108.2 (A), SW108.2
unnamed: D109.2 (A), SW109.2
unnamed: D110.2 (A), SW110.2
unnamed: D111.2 (A), SW111.2
unnamed: D112.2 (A), SW112.2
unnamed: D113.2 (A), SW113.2
unnamed: D114.2 (A), SW114.2
unnamed: D115.2 (A), SW115.2
unnamed: D116.2 (A), SW116.2
unnamed: D117.2 (A), SW117.2
unnamed: D118.2 (A), SW118.2
unnamed: D119.2 (A), SW119.2
unnamed: D120.2 (A), SW120.2
unnamed: D121.2 (A), SW121.2
unnamed: D122.2 (A), SW122.2
unnamed: D123.2 (A), SW123.2
unnamed: D124.2 (A), SW124.2
unnamed: D125.2 (A), SW125.2
unnamed: D126.2 (A), SW126.2
unnamed: D127.2 (A), SW127.2
unnamed: D128.2 (A), SW128.2
unnamed: D129.2 (A), SW129.2
unnamed: D130.2 (A), SW130.2
R_BAT: PSW1.2 (B), U1.1 (BATIN/P0.04)
R_CS: J1.5, U1.23 (RX1/P0.08)
R_ENCA: SW25.A, U1.5 (AIN7/P0.31)
R_ENCB: SW25.B, U1.6 (AIN5/P0.29)
R_RESET: RSW1.2, U1.3 (RST)
R_RGB: J2.2, U1.24 (TX0/P0.06)
R_SCL: J1.2, U1.19 (P0.20)
R_SDA: J1.1, U1.20 (P0.17)
R_SW25A: SW1.1, SW7.1, SW13.1, SW19.1, SW25.S1, U1.12 (NFC1/P0.09)
R_SW25B: D25.2 (A), SW25.S2
R_col0: SW6.1, SW12.1, SW18.1, SW24.1, SW30.1, U1.7 (AIN0/P0.02)
R_col1: SW5.1, SW11.1, SW17.1, SW23.1, SW29.1, U1.8 (P1.15)
R_col2: SW4.1, SW10.1, SW16.1, SW22.1, SW28.1, U1.9 (P1.13)
R_col3: SW3.1, SW9.1, SW15.1, SW21.1, SW27.1, U1.10 (P1.11)
R_col4: SW2.1, SW8.1, SW14.1, SW20.1, SW26.1, U1.11 (NFC2/P0.10)
R_row0: D1.1 (K), D2.1 (K), D3.1 (K), D4.1 (K), D5.1 (K), D6.1 (K), U1.17 (P0.24)
R_row1: D7.1 (K), D8.1 (K), D9.1 (K), D10.1 (K), D11.1 (K), D12.1 (K), U1.16 (P1.00)
R_row2: D13.1 (K), D14.1 (K), D15.1 (K), D16.1 (K), D17.1 (K), D18.1 (K), U1.15 (P0.11)
R_row3: D19.1 (K), D20.1 (K), D21.1 (K), D22.1 (K), D23.1 (K), D24.1 (K), U1.14 (P1.04)
R_row4: D25.1 (K), D26.1 (K), D27.1 (K), D28.1 (K), D29.1 (K), D30.1 (K), U1.13 (P1.06)
VCC: J1.3, J2.1, J101.3, J102.1, U1.4 (VCC), U101.4 (VCC)
